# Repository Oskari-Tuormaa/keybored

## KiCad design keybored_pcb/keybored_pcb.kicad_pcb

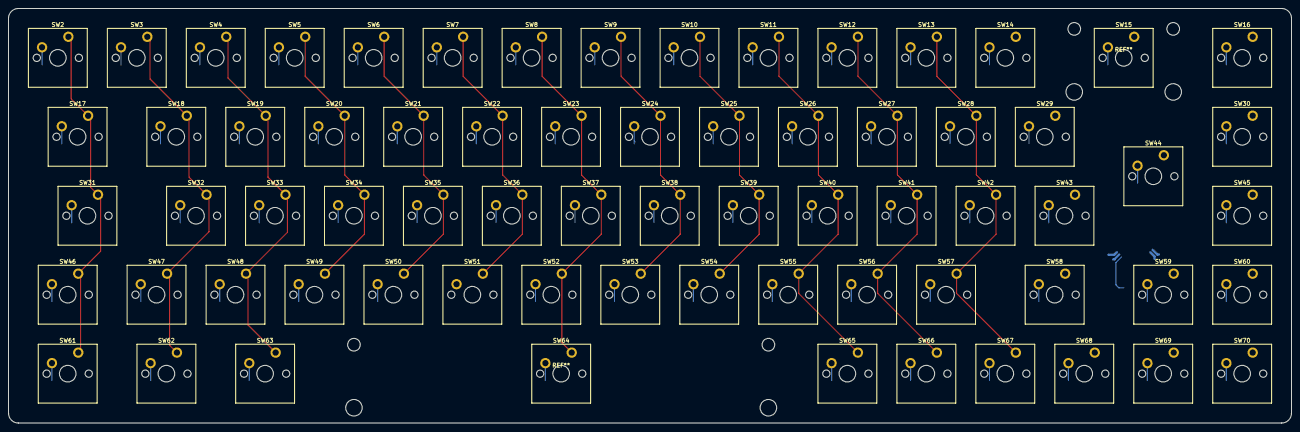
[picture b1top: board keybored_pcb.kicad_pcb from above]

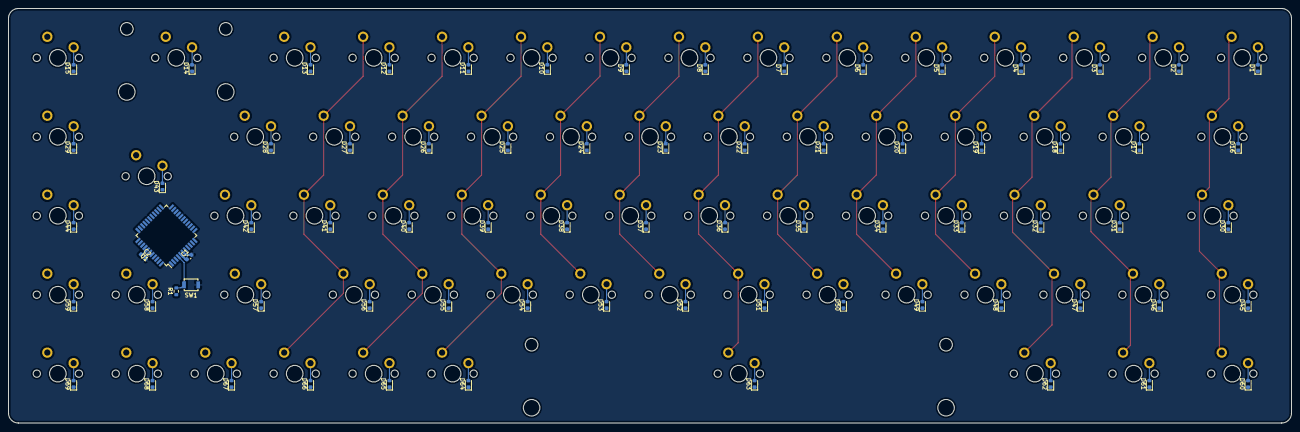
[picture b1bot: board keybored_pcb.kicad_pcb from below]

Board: 2 copper layers, 309.6 x 100.0 mm, 143 parts (5 on the bottom side), 92 nets.

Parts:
C1: 100n; C_0603_1608Metric
C2: 10u; C_0603_1608Metric
D1, D2, D3, D4, D5, D6, D7, D8, D9, D10, D11, D12, D13, D14, D15, D16, D17, D18, D19, D20, D21, D22, D23, D24, D25, D26, D27, D28, D29, D30, D31, D32, D33, D34, D35, D36, D37, D38, D39, D40, D41, D42, D43, D44, D45, D46, D47, D48, D49, D50, D51, D52, D53, D54, D55, D56, D57, D58, D59, D60, D61, D62, D63, D64, D65, D66, D67, D68, D69: D; D_0603_1608Metric
R1: 100k; R_0603_1608Metric
SW1: RESET; SW_SPST_B3U-1000P
SW2: caps; SW_Cherry_MX_PCB_1.00u
SW3: 1; SW_Cherry_MX_PCB_1.00u
SW4: 2; SW_Cherry_MX_PCB_1.00u
SW5: 3; SW_Cherry_MX_PCB_1.00u
SW6: 4; SW_Cherry_MX_PCB_1.00u
SW7: 5; SW_Cherry_MX_PCB_1.00u
SW8: 6; SW_Cherry_MX_PCB_1.00u
SW9: 7; SW_Cherry_MX_PCB_1.00u
SW10: 8; SW_Cherry_MX_PCB_1.00u
SW11: 9; SW_Cherry_MX_PCB_1.00u
SW12: 0; SW_Cherry_MX_PCB_1.00u
SW13: -; SW_Cherry_MX_PCB_1.00u
SW14: =; SW_Cherry_MX_PCB_1.00u
SW15: Backspace; SW_Cherry_MX_PCB_2.00u
SW16: LED; SW_Cherry_MX_PCB_1.00u
SW17: Tab; SW_Cherry_MX_PCB_1.50u
SW18: q; SW_Cherry_MX_PCB_1.00u
SW19: w; SW_Cherry_MX_PCB_1.00u
SW20: e; SW_Cherry_MX_PCB_1.00u
SW21: r; SW_Cherry_MX_PCB_1.00u
SW22: t; SW_Cherry_MX_PCB_1.00u
SW23: y; SW_Cherry_MX_PCB_1.00u
SW24: u; SW_Cherry_MX_PCB_1.00u
SW25: i; SW_Cherry_MX_PCB_1.00u
SW26: o; SW_Cherry_MX_PCB_1.00u
SW27: p; SW_Cherry_MX_PCB_1.00u
SW28: [; SW_Cherry_MX_PCB_1.00u
SW29: ]; SW_Cherry_MX_PCB_1.00u
SW30: home; SW_Cherry_MX_PCB_1.00u
SW31: esc; SW_Cherry_MX_PCB_1.75u
SW32: a; SW_Cherry_MX_PCB_1.00u
SW33: s; SW_Cherry_MX_PCB_1.00u
SW34: d; SW_Cherry_MX_PCB_1.00u
SW35: f; SW_Cherry_MX_PCB_1.00u
SW36: g; SW_Cherry_MX_PCB_1.00u
SW37: h; SW_Cherry_MX_PCB_1.00u
SW38: j; SW_Cherry_MX_PCB_1.00u
SW39: k; SW_Cherry_MX_PCB_1.00u
SW40: l; SW_Cherry_MX_PCB_1.00u
SW41: ;; SW_Cherry_MX_PCB_1.00u
SW42: @; SW_Cherry_MX_PCB_1.00u
SW43: #; SW_Cherry_MX_PCB_1.00u
SW44: Enter; SW_Cherry_MX_PCB_ISOEnter
SW45: page up; SW_Cherry_MX_PCB_1.00u
SW46: shift; SW_Cherry_MX_PCB_1.25u
SW47: \; SW_Cherry_MX_PCB_1.00u
SW48: z; SW_Cherry_MX_PCB_1.00u
SW49: x; SW_Cherry_MX_PCB_1.00u
SW50: c; SW_Cherry_MX_PCB_1.00u
SW51: v; SW_Cherry_MX_PCB_1.00u
SW52: b; SW_Cherry_MX_PCB_1.00u
SW53: n; SW_Cherry_MX_PCB_1.00u
SW54: m; SW_Cherry_MX_PCB_1.00u
SW55: ,; SW_Cherry_MX_PCB_1.00u
SW56: .; SW_Cherry_MX_PCB_1.00u
SW57: /; SW_Cherry_MX_PCB_1.00u
SW58: rshift; SW_Cherry_MX_PCB_1.75u
SW59: up; SW_Cherry_MX_PCB_1.00u
SW60: page down; SW_Cherry_MX_PCB_1.00u
SW61: ctrl; SW_Cherry_MX_PCB_1.25u
SW62: win; SW_Cherry_MX_PCB_1.25u
SW63: alt; SW_Cherry_MX_PCB_1.25u
SW64: space; SW_Cherry_MX_PCB_6.25u
SW65: ralt; SW_Cherry_MX_PCB_1.00u
SW66: rwin; SW_Cherry_MX_PCB_1.00u
SW67: rctrl; SW_Cherry_MX_PCB_1.00u
SW68: left; SW_Cherry_MX_PCB_1.00u
SW69: down; SW_Cherry_MX_PCB_1.00u
SW70: right; SW_Cherry_MX_PCB_1.00u
U1: ATmega32-16A; TQFP-44_10x10mm_P0.8mm

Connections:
+5V: C1.1, C2.1, R1.1, U1.5 (VCC), U1.17 (VCC), U1.38 (VCC)
/Keyboard Matrix/C1: SW2.2 (B), SW17.2 (B), SW31.2 (B), SW46.2 (B), SW61.2 (B)
/Keyboard Matrix/C2: SW3.2 (B), SW18.2 (B), SW32.2 (B), SW47.2 (B), SW62.2 (B)
/Keyboard Matrix/C3: SW4.2 (B), SW19.2 (B), SW33.2 (B), SW48.2 (B), SW63.2 (B)
/Keyboard Matrix/C4: SW5.2 (B), SW20.2 (B), SW34.2 (B), SW49.2 (B)
/Keyboard Matrix/C5: SW6.2 (B), SW21.2 (B), SW35.2 (B), SW50.2 (B)
/Keyboard Matrix/C6: SW7.2 (B), SW22.2 (B), SW36.2 (B), SW51.2 (B)
/Keyboard Matrix/C7: SW8.2 (B), SW23.2 (B), SW37.2 (B), SW52.2 (B), SW64.2 (B)
/Keyboard Matrix/C8: SW9.2 (B), SW24.2 (B), SW38.2 (B), SW53.2 (B)
/Keyboard Matrix/C9: SW10.2 (B), SW25.2 (B), SW39.2 (B), SW54.2 (B)
/Keyboard Matrix/C10: SW11.2 (B), SW26.2 (B), SW40.2 (B), SW55.2 (B), SW65.2 (B)
/Keyboard Matrix/C11: SW12.2 (B), SW27.2 (B), SW41.2 (B), SW56.2 (B), SW66.2 (B)
/Keyboard Matrix/C12: SW13.2 (B), SW28.2 (B), SW42.2 (B), SW57.2 (B), SW67.2 (B)
/Keyboard Matrix/C13: SW14.2 (B), SW29.2 (B), SW43.2 (B), SW58.2 (B), SW68.2 (B)
/Keyboard Matrix/C14: SW15.2 (B), SW44.2 (B), SW59.2 (B), SW69.2 (B)
/Keyboard Matrix/C15: SW16.2 (B), SW30.2 (B), SW45.2 (B), SW60.2 (B), SW70.2 (B)
/Keyboard Matrix/R1: D1.1 (K), D2.1 (K), D3.1 (K), D4.1 (K), D5.1 (K), D6.1 (K), D7.1 (K), D8.1 (K), D9.1 (K), D10.1 (K), D11.1 (K), D12.1 (K), D13.1 (K), D14.1 (K), D15.1 (K)
/Keyboard Matrix/R2: D16.1 (K), D17.1 (K), D18.1 (K), D19.1 (K), D20.1 (K), D21.1 (K), D22.1 (K), D23.1 (K), D24.1 (K), D25.1 (K), D26.1 (K), D27.1 (K), D28.1 (K), D29.1 (K)
/Keyboard Matrix/R3: D30.1 (K), D31.1 (K), D32.1 (K), D33.1 (K), D34.1 (K), D35.1 (K), D36.1 (K), D37.1 (K), D38.1 (K), D39.1 (K), D40.1 (K), D41.1 (K), D42.1 (K), D43.1 (K), D44.1 (K)
/Keyboard Matrix/R4: D45.1 (K), D46.1 (K), D47.1 (K), D48.1 (K), D49.1 (K), D50.1 (K), D51.1 (K), D52.1 (K), D53.1 (K), D54.1 (K), D55.1 (K), D56.1 (K), D57.1 (K), D58.1 (K), D59.1 (K)
/Keyboard Matrix/R5: D60.1 (K), D61.1 (K), D62.1 (K), D63.1 (K), D64.1 (K), D65.1 (K), D66.1 (K), D67.1 (K), D68.1 (K), D69.1 (K)
/RESET: R1.2, SW1.2 (B), U1.4 (~RESET)
Earth: C1.2, C2.2, SW1.1 (A), U1.6 (GND), U1.18 (GND), U1.28 (GND), U1.39 (GND)
unnamed: D1.2 (A), SW2.1 (A)
unnamed: D2.2 (A), SW3.1 (A)
unnamed: D3.2 (A), SW4.1 (A)
unnamed: D4.2 (A), SW5.1 (A)
unnamed: D5.2 (A), SW6.1 (A)
unnamed: D6.2 (A), SW7.1 (A)
unnamed: D7.2 (A), SW8.1 (A)
unnamed: D8.2 (A), SW9.1 (A)
unnamed: D9.2 (A), SW10.1 (A)
unnamed: D10.2 (A), SW11.1 (A)
unnamed: D11.2 (A), SW12.1 (A)
unnamed: D12.2 (A), SW13.1 (A)
unnamed: D13.2 (A), SW14.1 (A)
unnamed: D14.2 (A), SW15.1 (A)
unnamed: D15.2 (A), SW16.1 (A)
unnamed: D16.2 (A), SW17.1 (A)
unnamed: D17.2 (A), SW18.1 (A)
unnamed: D18.2 (A), SW19.1 (A)
unnamed: D19.2 (A), SW20.1 (A)
unnamed: D20.2 (A), SW21.1 (A)
unnamed: D21.2 (A), SW22.1 (A)
unnamed: D22.2 (A), SW23.1 (A)
unnamed: D23.2 (A), SW24.1 (A)
unnamed: D24.2 (A), SW25.1 (A)
unnamed: D25.2 (A), SW26.1 (A)
unnamed: D26.2 (A), SW27.1 (A)
unnamed: D27.2 (A), SW28.1 (A)
unnamed: D28.2 (A), SW29.1 (A)
unnamed: D29.2 (A), SW30.1 (A)
unnamed: D30.2 (A), SW31.1 (A)
unnamed: D31.2 (A), SW32.1 (A)
unnamed: D32.2 (A), SW33.1 (A)
unnamed: D33.2 (A), SW34.1 (A)
unnamed: D34.2 (A), SW35.1 (A)
unnamed: D35.2 (A), SW36.1 (A)
unnamed: D36.2 (A), SW37.1 (A)
unnamed: D37.2 (A), SW38.1 (A)
unnamed: D38.2 (A), SW39.1 (A)
unnamed: D39.2 (A), SW40.1 (A)
unnamed: D40.2 (A), SW41.1 (A)
unnamed: D41.2 (A), SW42.1 (A)
unnamed: D42.2 (A), SW43.1 (A)
unnamed: D43.2 (A), SW44.1 (A)
unnamed: D44.2 (A), SW45.1 (A)
unnamed: D45.2 (A), SW46.1 (A)
unnamed: D46.2 (A), SW47.1 (A)
unnamed: D47.2 (A), SW48.1 (A)
unnamed: D48.2 (A), SW49.1 (A)
unnamed: D49.2 (A), SW50.1 (A)
unnamed: D50.2 (A), SW51.1 (A)
unnamed: D51.2 (A), SW52.1 (A)
unnamed: D52.2 (A), SW53.1 (A)
unnamed: D53.2 (A), SW54.1 (A)
unnamed: D54.2 (A), SW55.1 (A)
unnamed: D55.2 (A), SW56.1 (A)
unnamed: D56.2 (A), SW57.1 (A)
unnamed: D57.2 (A), SW58.1 (A)
unnamed: D58.2 (A), SW59.1 (A)
unnamed: D59.2 (A), SW60.1 (A)
unnamed: D60.2 (A), SW61.1 (A)
unnamed: D61.2 (A), SW62.1 (A)
unnamed: D62.2 (A), SW63.1 (A)
unnamed: D63.2 (A), SW64.1 (A)
unnamed: D64.2 (A), SW65.1 (A)
unnamed: D65.2 (A), SW66.1 (A)
unnamed: D66.2 (A), SW67.1 (A)
unnamed: D67.2 (A), SW68.1 (A)
unnamed: D68.2 (A), SW69.1 (A)
unnamed: D69.2 (A), SW70.1 (A)

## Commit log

2022-09-11 Add initial KiCAD PCB files
2022-09-11 Add GIMP keyboard matrix file
2022-09-11 Add keyboard-layout-editor.com .json file
